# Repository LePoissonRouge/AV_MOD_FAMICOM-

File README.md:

# AV_MOD_FAMICOM-
FAMICOM VIDEO MOD CARD

This board is a replacement for the RF + Power supply board on the famicom

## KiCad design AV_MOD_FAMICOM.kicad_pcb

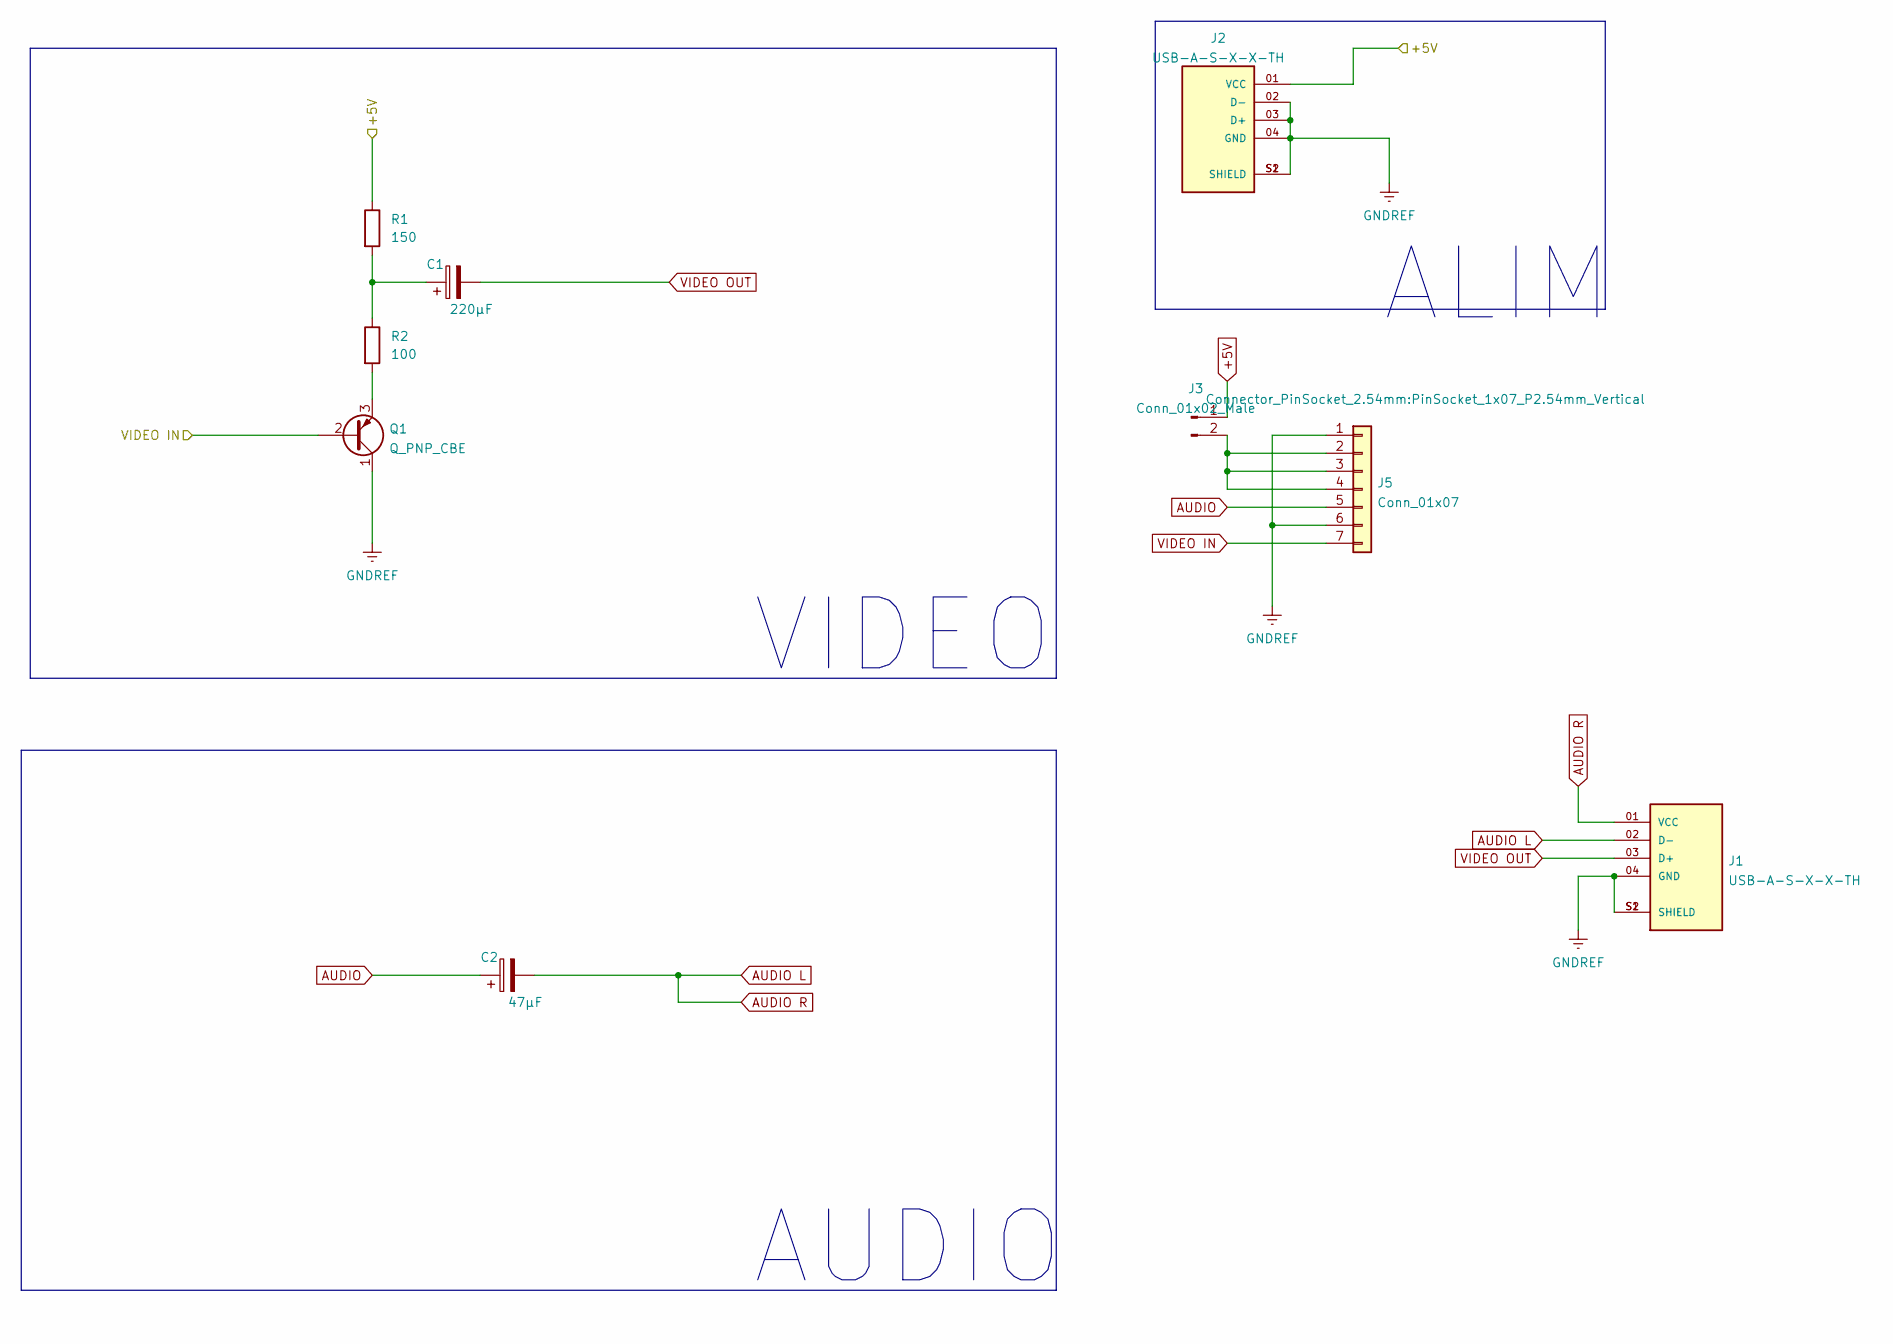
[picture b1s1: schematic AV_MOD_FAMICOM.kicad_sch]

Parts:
C1: 220µF; CP_Radial_D8.0mm_P5.00mm
C2: 47µF; CP_Radial_D8.0mm_P5.00mm
J1, J2: USB-A-S-X-X-TH; SAMTEC_USB-A-S-X-X-TH; PARTREV R
J3: Conn_01x02_Male; PinHeader_1x02_P2.54mm_Vertical
J5: Conn_01x07; PinSocket_1x07_P2.54mm_Vertical
Q1: Q_PNP_CBE; TO-92
R1: 150; R_Axial_DIN0207_L6.3mm_D2.5mm_P10.16mm_Horizontal
R2: 100; R_Axial_DIN0207_L6.3mm_D2.5mm_P10.16mm_Horizontal

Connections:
+5V: J2.01 (VCC), J3.1, R1.1
AUDIO: C2.1, J5.5
AUDIO L: C2.2, J1.01 (VCC), J1.02 (D-)
GNDREF: J1.04 (GND), J1.S1 (SHIELD), J1.S2 (SHIELD), J2.02 (D-), J2.03 (D+), J2.04 (GND), J2.S1 (SHIELD), J2.S2 (SHIELD), J5.1, J5.6, Q1.1 (C)
unnamed: C1.1, R1.2, R2.1
unnamed: J3.2, J5.2, J5.3, J5.4
unnamed: Q1.3 (E), R2.2
VIDEO IN: J5.7, Q1.2 (B)
VIDEO OUT: C1.2, J1.03 (D+)

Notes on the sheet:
AUDIO
VIDEO
ALIM

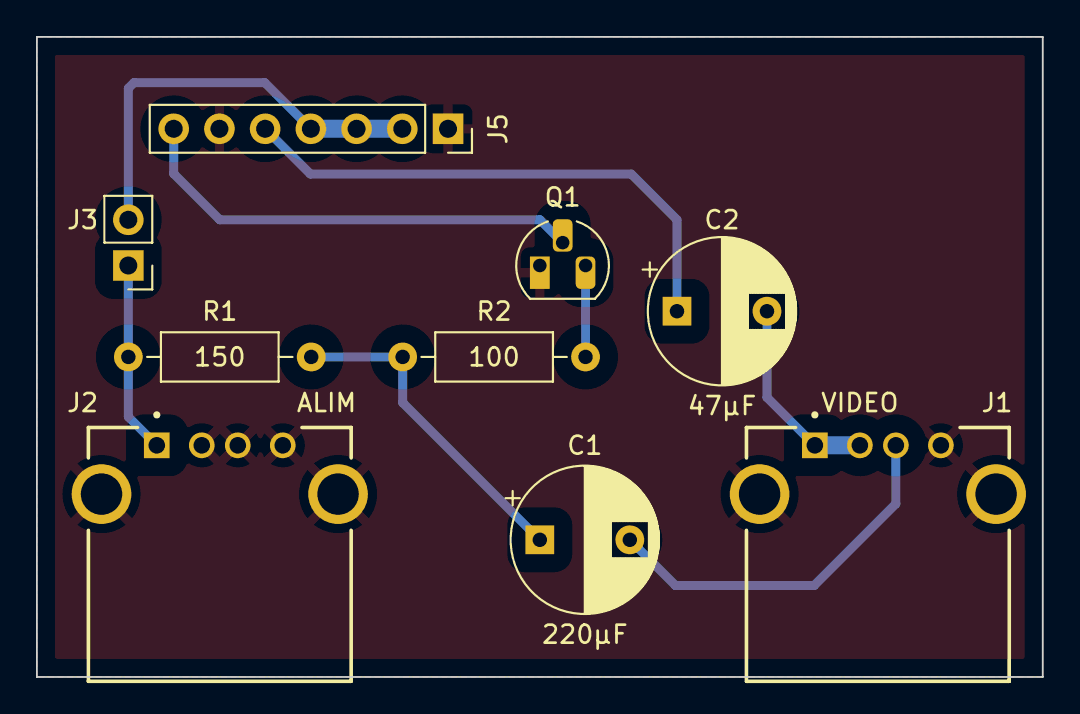
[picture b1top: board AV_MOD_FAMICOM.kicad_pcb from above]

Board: 2 copper layers, 55.9 x 35.6 mm, 9 parts (0 on the bottom side), 9 nets.

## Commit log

2022-12-02 Add files via upload
    New version of the board
